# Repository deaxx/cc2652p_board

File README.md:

# cc2652p_board
mini-dev board on E72-2G4M20S1E

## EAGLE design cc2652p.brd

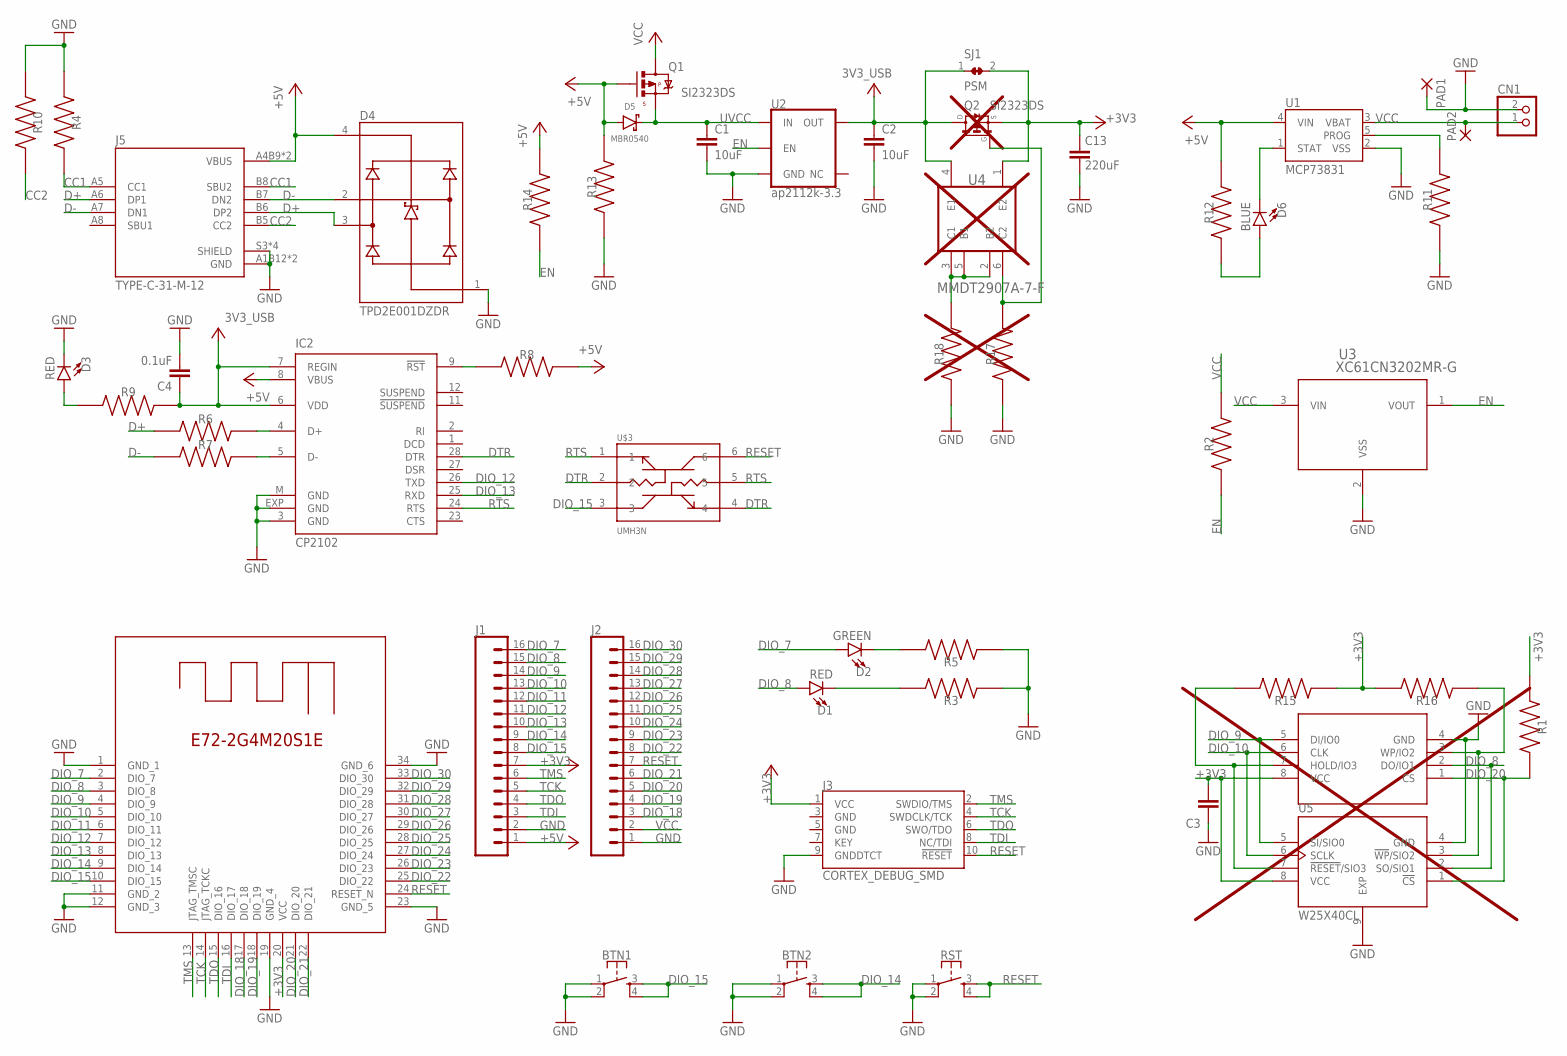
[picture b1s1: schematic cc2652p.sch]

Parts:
BTN1, BTN2: MOMENTARY-SWITCH-SPST-2-SMD-4.6X2.8MM; TACTILE_SWITCH_SMD_4.6X2.8MM
C1, C2: 10uF; 0603
C3: 100n; CAPC1005X40N
C4: 0.1uF; 0603
C13: 220uF; CAPM7343X310
CN1: JST_2PIN-SMT-RA; JST-PH-2-SMT-RA
D1, D3: RED; LED-0603
D2: GREEN; LED-0603
D4: TPD2E001DZDR; SOT192P237X122-4N
D5: MBR0540; SOD-323
D6: BLUE; LED-0603
IC2: CP2102; MLP28
J1, J2: CONN_161X16_NO_SILK; 1X16_NO_SILK
J3: CORTEX_DEBUG_SMD; SAMTECH_FTSH-105-01
J5: TYPE-C-31-M-12; HRO_TYPE-C-31-M-12
PAD1, PAD2: WIREPADSMD1,27-254; SMD1,27-2,54
Q1, Q2: SI2323DS; SOT23
R1, R13, R17, R18: 100k; RESC1005X40N
R2, R14, R15, R16: 10k; RESC1005X40N
R3, R5, R9, R12: 2.2k; RESC1005X40N
R4, R10: 5.1k; RESC1005X40N
R6, R7: 33Ohm; RESC1005X40N
R8: 4.7k; RESC1005X40N
R11: 2k; RESC1005X40N
RST: MOMENTARY-SWITCH-SPST-2-SMD-4.6X2.8MM; TACTILE_SWITCH_SMD_4.6X2.8MM
SJ1: PSM; SMALL_SOLDER_JUMPER_CLOSED
U1: MCP73831; SOT23-5
U2: ap2112k-3.3; SOT23-5
U3: XC61CN3202MR-G; XC61C_SOT-23_TOR
U4: MMDT2907A-7-F; SOT65P210X110-6N
U5: W25X40CL; PSON50P200X300X60-9N
U$1: E72-2G4M20S1E
U$2: MX25R8035FM1IL0; SO-8
U$3: UMH3N; SOP65P210X100-6N

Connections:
+3V3: C3.2, C13.1, J1.7, J3.1 (VCC), Q2.2 (S), R1.1, R15.1, R16.2, SJ1.2, U4.1 (E2), U5.8 (VCC), U$1.20 (VCC), U$2.8 (VCC)
+5V: D4.4 (VCC), D5.A, IC2.8 (VBUS), J1.1, J5.A4B9 (VBUS), J5.B4A9 (VBUS), Q1.1 (G), R8.2, R12.2, R13.2, R14.2, U1.4 (VIN)
CC1: J5.A5 (CC1), J5.B8 (SBU2), R4.2
CC2: J5.B5 (CC2), R10.2
D+: D4.3 (IO2), J5.A6 (DP1), J5.B6 (DP2), R6.1
D-: D4.2 (IO1), J5.A7 (DN1), J5.B7 (DN2), R7.1
DIO_7: D2.A, J1.16, U$1.2 (DIO_7)
DIO_8: D1.A, J1.15, U5.2 (SO/SIO1), U$1.3 (DIO_8), U$2.2 (DO/IO1)
DIO_9: J1.14, U5.5 (SI/SIO0), U$1.4 (DIO_9), U$2.5 (DI/IO0)
DIO_10: J1.13, U5.6 (SCLK), U$1.5 (DIO_10), U$2.6 (CLK)
DIO_11: J1.12, U$1.6 (DIO_11)
DIO_12: IC2.26 (TXD), J1.11, U$1.7 (DIO_12)
DIO_13: IC2.25 (RXD), J1.10, U$1.8 (DIO_13)
DIO_14: BTN2.3, BTN2.4, J1.9, U$1.9 (DIO_14)
DIO_15: BTN1.3, BTN1.4, J1.8, U$1.10 (DIO_15), U$3.3
DIO_18: J2.3, U$1.17 (DIO_18)
DIO_19: J2.4, U$1.18 (DIO_19)
DIO_20: J2.5, R1.2, U5.1 (!CS), U$1.21 (DIO_20), U$2.1 (CS)
DIO_21: J2.6, U$1.22 (DIO_21)
DIO_22: J2.8, U$1.25 (DIO_22)
DIO_23: J2.9, U$1.26 (DIO_23)
DIO_24: J2.10, U$1.27 (DIO_24)
DIO_25: J2.11, U$1.28 (DIO_25)
DIO_26: J2.12, U$1.29 (DIO_26)
DIO_27: J2.13, U$1.30 (DIO_27)
DIO_28: J2.14, U$1.31 (DIO_28)
DIO_29: J2.15, U$1.32 (DIO_29)
DIO_30: J2.16, U$1.33 (DIO_30)
DTR: IC2.28 (DTR), U$3.2, U$3.4
EN: R2.1, R14.1, U2.3 (EN), U3.1 (VOUT)
GND: BTN1.1, BTN1.2, BTN2.1, BTN2.2, C1.2, C2.2, C3.1, C4.2, C13.2, CN1.2 (1), D3.C, D4.1 (GND), IC2.3 (GND), IC2.EXP (GND), IC2.M (GND), J1.2, J2.1, J3.9 (GNDDTCT), J5.A1B12 (GND), J5.B1A12 (GND), J5.S3 (SHIELD), J5.S4 (SHIELD), J5.S5 (SHIELD), J5.S6 (SHIELD), PAD1.1, R3.1, R4.1, R5.1, R10.1, R11.1, R13.1, R17.1, R18.1, RST.1, RST.2, U1.2 (VSS), U2.2 (GND), U3.2 (VSS), U5.4 (GND), U5.9 (EXP), U$1.1 (GND_1), U$1.11 (GND_2), U$1.12 (GND_3), U$1.19 (GND_4), U$1.23 (GND_5), U$1.34 (GND_6), U$2.4 (GND)
unnamed: IC2.9 (!RST), R8.1
unnamed: D1.C, R3.2
unnamed: D2.C, R5.2
unnamed: R18.2, U4.2 (B2), U4.3 (C1), U4.5 (B1)
unnamed: IC2.4 (D+), R6.2
unnamed: IC2.5 (D-), R7.2
unnamed: D3.A, R9.2
unnamed: R11.2, U1.5 (PROG)
unnamed: D6.A, R12.1
unnamed: Q2.1 (G), R17.2, U4.6 (C2)
unnamed: D6.C, U1.1 (STAT)
unnamed: R15.2, U5.7 (!RESET!/SIO3), U$2.7 (HOLD/IO3)
unnamed: R16.1, U5.3 (!WP!/SIO2), U$2.3 (WP/IO2)
RESET: J2.7, J3.10 (!RESET), RST.3, RST.4, U$1.24 (RESET_N), U$3.6
RTS: IC2.24 (RTS), U$3.1, U$3.5
TCK: J1.5, J3.4 (SWDCLK/TCK), U$1.14 (JTAG_TCKC)
TDI: J1.3, J3.8 (NC/TDI), U$1.16 (DIO_17)
TDO: J1.4, J3.6 (SWO/TDO), U$1.15 (DIO_16)
TMS: J1.6, J3.2 (SWDIO/TMS), U$1.13 (JTAG_TMSC)
UVCC: C1.1, D5.C, Q1.2 (S), U2.1 (IN)
V+: C2.1, C4.1, IC2.6 (VDD), IC2.7 (REGIN), Q2.3 (D), R9.1, SJ1.1, U2.5 (OUT), U4.4 (E1)
VCC: CN1.1 (2), J2.2, PAD2.1, Q1.3 (D), R2.2, U1.3 (VBAT), U3.3 (VIN)

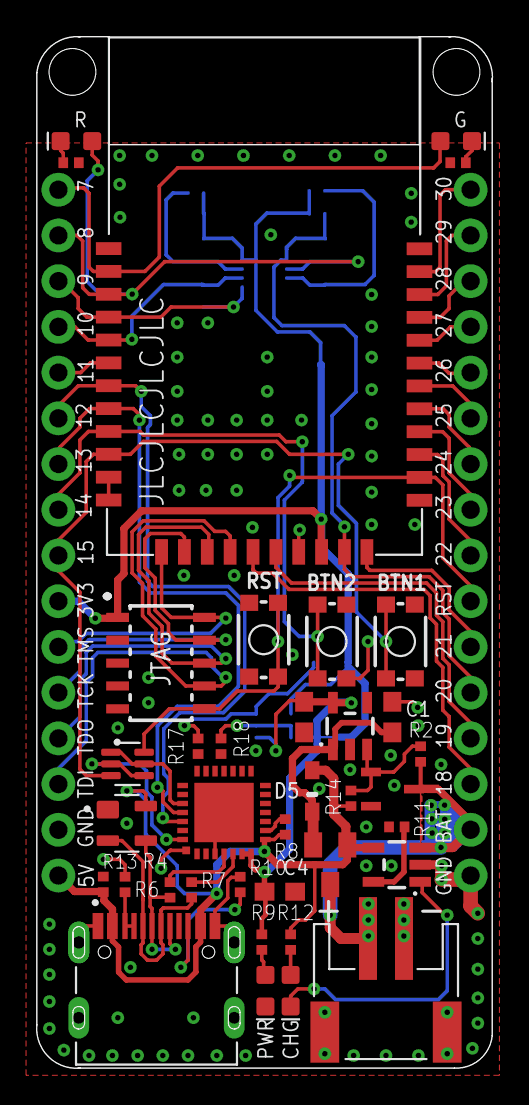
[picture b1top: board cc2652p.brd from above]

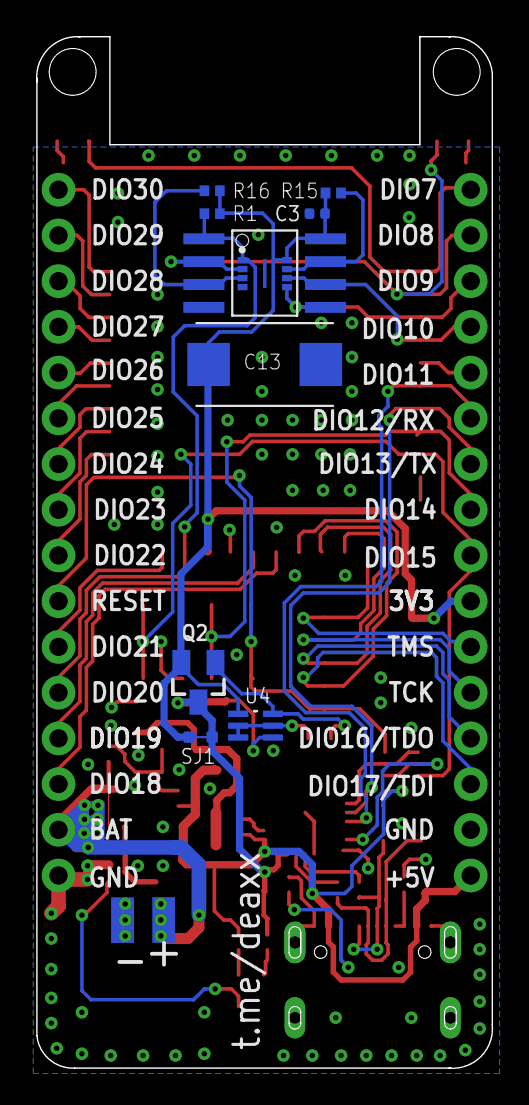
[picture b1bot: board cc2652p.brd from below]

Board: 2 copper layers, 25.3 x 57.3 mm, 51 parts (12 on the bottom side), 53 nets.

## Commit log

2022-04-25 Add files via upload
    RX TX fix

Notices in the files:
parts and their libraries:
SparkFun-Connectors: Licensing: Creative Commons ShareAlike 4.0 International - https://creativecommons.org/licenses/by-sa/4.0
